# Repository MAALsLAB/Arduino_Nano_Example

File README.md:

# Arduino_Nano_Example
2-layers PCB Design Practice

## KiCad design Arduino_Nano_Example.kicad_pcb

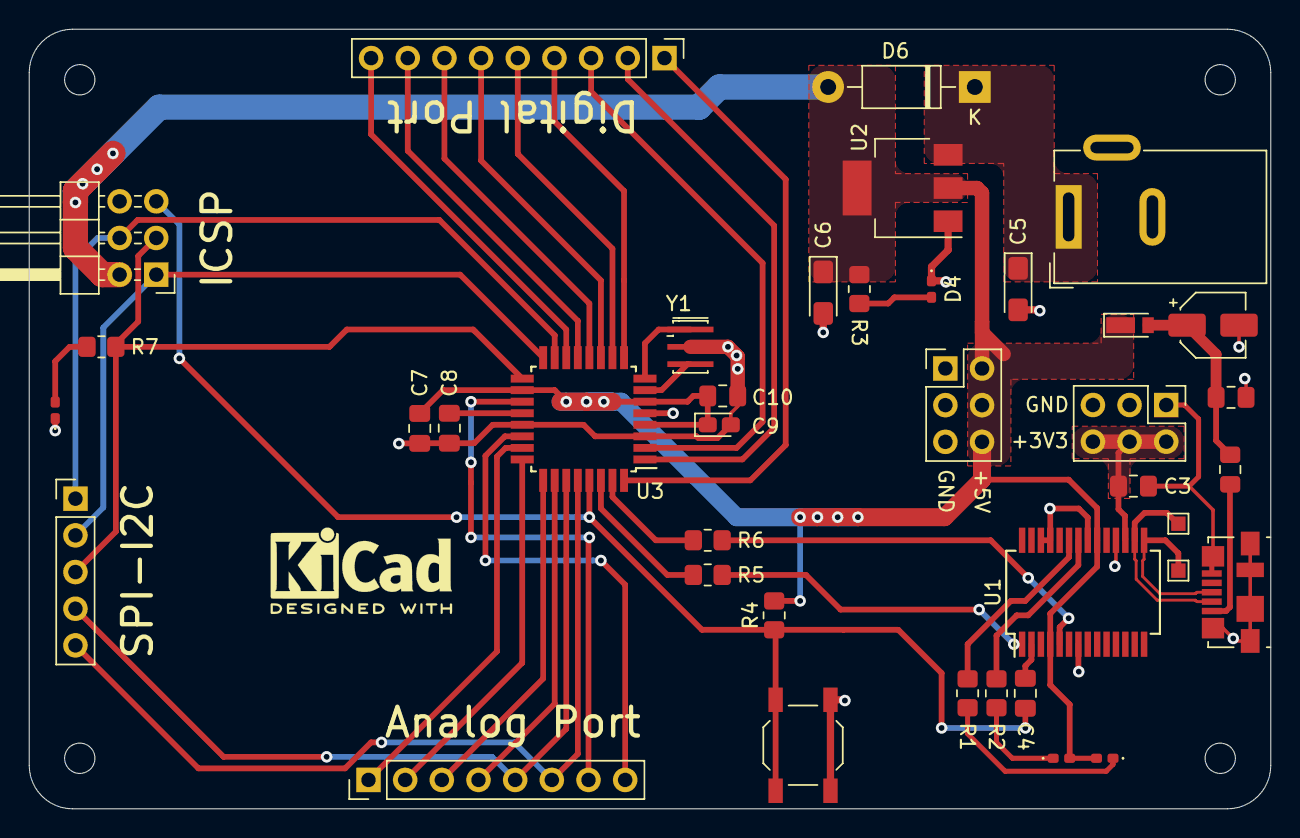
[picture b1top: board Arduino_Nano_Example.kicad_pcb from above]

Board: 2 copper layers, 86.0 x 54.0 mm, 43 parts (0 on the bottom side), 43 nets.

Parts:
C1, C3, C4, C8: 100nF; C_0805_2012Metric_Pad1.18x1.45mm_HandSolder
C2: 4.7uF; CP_Elec_4x3
C5, C6: 10uF; CP_EIA-3216-10_Kemet-I_Pad1.58x1.35mm_HandSolder
C7, C10: 1uF; C_0805_2012Metric_Pad1.18x1.45mm_HandSolder
C9: 4.7uF; CP_EIA-1608-08_AVX-J_Pad1.25x1.05mm_HandSolder
D1: SS1P3L; D_TUMD2
D2: Red; LED_0402_1005Metric_Pad0.77x0.64mm_HandSolder
D3, D4: Green; LED_0402_1005Metric_Pad0.77x0.64mm_HandSolder
D5: Yellow; LED_0402_1005Metric_Pad0.77x0.64mm_HandSolder
D6: 1N4007; D_DO-41_SOD81_P10.16mm_Horizontal
F1: SMD0603P050TF; Fuse_0805_2012Metric_Pad1.15x1.40mm_HandSolder
H1, H2, H3, H4: MountingHole; MountingHole_2.1mm
J1: Conn_02x03_Odd_Even; PinHeader_2x03_P2.54mm_Horizontal
J2: Molex_47346-0001; USB_Micro-B_Molex_47346-0001
J3: Barrel_Jack_Switch; BarrelJack_Wuerth_6941xx301002
J4: SPI|I2C; PinHeader_1x05_P2.54mm_Vertical
J5: Ananlog Port; PinHeader_1x08_P2.54mm_Vertical
J6, J8: Conn_02x03_Odd_Even; PinHeader_2x03_P2.54mm_Vertical
J7: Digital Port; PinHeader_1x09_P2.54mm_Vertical
R1, R2, R3, R4, R5, R6, R7: 1k; R_0805_2012Metric_Pad1.20x1.40mm_HandSolder
SW1: RESET; SW_SPST_TL3342
TP1: D+; TestPoint_Pad_1.0x1.0mm
TP2: D-; TestPoint_Pad_1.0x1.0mm
U1: FT232RL; SSOP-28_5.3x10.2mm_P0.65mm
U2: LM1117-5.0; SOT-223-3_TabPin2
U3: ATmega328P-AU; TQFP-32_7x7mm_P0.8mm
Y1: 16MHz; Resonator_SMD_muRata_CSTxExxV-3Pin_3.0x1.1mm_HandSoldering

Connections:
+3V3: C3.1, J8.2, J8.4, J8.6, U1.17
+5V: C6.1, C7.1, C9.1, C10.1, D1.1, D2.2, D3.2, D6.2, J1.2, J6.2, J6.4, J6.6, R3.2, R4.2, U1.4, U1.20, U2.2, U3.4, U3.6, U3.18
/A0: J5.1, U3.23
/A1: J5.2, U3.24
/A2: J5.3, U3.25
/A3: J5.4, U3.26
/A4: J4.4, J5.5, U3.27
/A5: J4.5, J5.6, U3.28
/A6: J5.7, U3.19
/A7: J5.8, U3.22
/ATmega328P/AREF: C8.1, U3.20
/ATmega328P/D0|RX: R5.2, U3.30
/ATmega328P/D1|TX: R6.2, U3.31
/D2: J7.1, U3.32
/D3: J7.2, U3.1
/D4: J7.3, U3.2
/D5: J7.4, U3.9
/D6: J7.5, U3.10
/D7: J7.6, U3.11
/D8: J7.7, U3.12
/D9: J7.8, U3.13
/D10: J7.9, U3.14
/RXD: R6.1, U1.5
/TXD: R5.1, U1.1
/USB_Interface/USB_N: J2.2, TP2.1, U1.16
/USB_Interface/USB_P: J2.3, TP1.1, U1.15
/~RESET: C4.1, J1.5, R4.1, SW1.1, U3.29
D11: J1.4, J4.1, U3.15
D12: J1.1, J4.2, U3.16
D13: J1.3, J4.3, R7.2, U3.17
GND: C1.2, C2.2, C3.2, C5.2, C6.2, C7.2, C8.2, C9.2, C10.2, D4.1, D5.1, J1.6, J2.5, J2.6, J3.2, J3.3, J6.1, J6.3, J6.5, J8.1, J8.3, J8.5, SW1.2, U1.7, U1.18, U1.21, U1.25, U1.26, U2.1, U3.3, U3.5, U3.21, Y1.2
unnamed: C4.2, U1.2
unnamed: D2.1, R1.1
unnamed: D3.1, R2.1
unnamed: D4.2, R3.1
unnamed: D5.2, R7.1
unnamed: F1.2, J2.1
unnamed: R1.2, U1.23
unnamed: R2.2, U1.22
unnamed: U3.7, Y1.3
unnamed: U3.8, Y1.1
VBUS: C1.1, C2.1, D1.2, F1.1
VDC: C5.1, D6.1, J3.1, U2.3

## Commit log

2021-10-13 Adding Project Files
2021-10-13 Set theme jekyll-theme-architect
2021-10-13 Set theme jekyll-theme-hacker
2021-10-13 Set theme jekyll-theme-slate
2021-10-13 Managing project Folders
2021-10-13 change the name of Arduino_Nanao_Example.html into index.html
